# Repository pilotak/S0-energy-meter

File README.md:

# S0 energy meter
ESP8266 based pulse counter for home utility meter compatible with ESPHome, Tasmota, etc.

## Basic model

**Features**:
- 230V direct power supply
- 5x S0 pulse meter input
- [ESPHome config](./config/S0-energy-meter.yaml)

## Enhanced model

**Features**:
- 230V direct power supply
- 1x S0 pulse meter input
- 2x input ie. for button or door sensor
- 1x SSR relay for light
- doorbell detection
- [ESPHome config](./config/S0-energy-meter-switch.yaml)

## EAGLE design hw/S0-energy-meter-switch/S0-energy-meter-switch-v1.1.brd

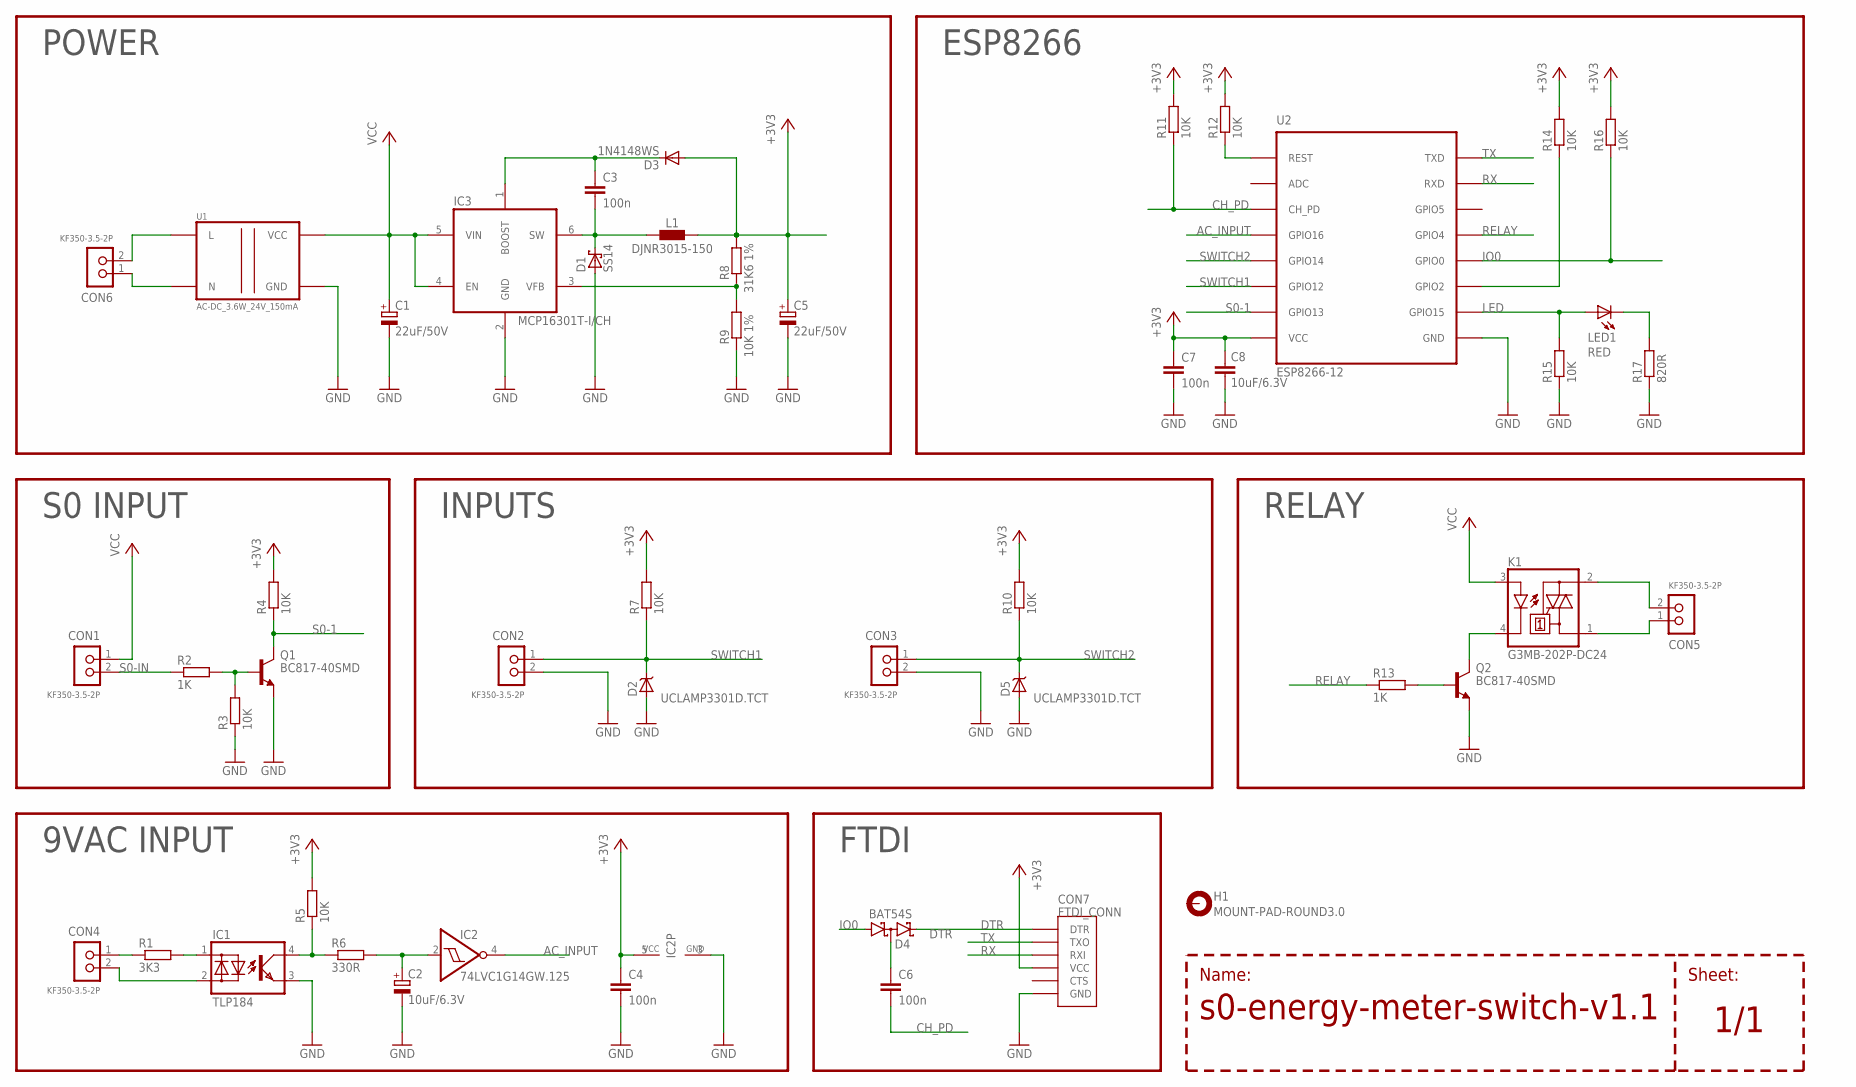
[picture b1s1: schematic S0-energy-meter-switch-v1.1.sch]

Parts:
C1, C5: 22uF/50V; PANASONIC_C
C2: 10uF/6.3V; CT3528
C3, C4, C6, C7: 100n; C0805
C8: 10uF/6.3V; C0805
CON1, CON2, CON3, CON4, CON5, CON6: KF350-3.5-2P; KF350-3.50-2P
CON7: FTDI_CONN; FTDI
D1: SS14; DO214AC
D2, D5: UCLAMP3301D.TCT; SOD323
D3: 1N4148WS; SOD323
D4: BAT54S; SOT23
H1: MOUNT-PAD-ROUND3.0; 3,0-PAD
IC1: TLP184; SOP04
IC2: 74LVC1G14GW.125; SC70-5
IC3: MCP16301T-I/CH; SOT23-6
K1: G3MB-202P-DC24; G3MB
L1: DJNR3015-150; L3015
LED1: RED; LED0805
Q1, Q2: BC817-40SMD; SOT23-BEC
R1: 3K3; R1206
R2, R13: 1K; R0805
R3, R4, R5, R7, R10, R11, R12, R14, R15, R16: 10K; R0805
R6: 330R; R0805
R8: 31K6 1%; R0805
R9: 10K 1%; R0805
R17: 820R; R0805
U1: AC-DC_3.6W_24V_150mA; AC_DC_24V_150MA
U2: ESP8266-12; ESP-12

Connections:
4: IC1.1 (A), R1.2
+3V3: C4.1, C5.+, C7.1, C8.1, CON7.P$4 (VCC), D3.A, IC2.5 (VCC), L1.1, R4.2, R5.2, R7.2, R8.2, R10.2, R11.2, R12.2, R14.2, R16.2, U2.VCC
AC_INPUT: IC2.4 (O), U2.GPIO16
CH: C6.1, D4.3 (C1A2)
CH_PD: C6.2, R11.1, U2.CH_PD
DTR: CON7.P$1 (DTR), D4.2 (C2)
GND: C1.-, C2.-, C4.2, C5.-, C7.2, C8.2, CON2.2, CON3.2, CON7.P$6 (GND), D1.A, D2.A, D5.A, IC1.3 (EMIT), IC2.3 (GND), IC3.2 (GND), Q1.E, Q2.E, R3.1, R9.1, R15.1, R17.1, U1.GND, U2.GND
IO0: D4.1 (A1), R16.1, U2.GPIO0
L: CON6.2, U1.L
LED: LED1.A, R15.2, U2.GPIO15
N: CON6.1, U1.N
unnamed: LED1.C, R17.2
unnamed: CON5.1, K1.1 (A1)
unnamed: Q1.B, R2.2, R3.2
unnamed: C2.+, IC2.2 (I), R6.2
unnamed: CON5.2, K1.2 (A2)
unnamed: CON4.2, IC1.2 (C)
unnamed: IC1.4 (COL), R5.1, R6.1
unnamed: K1.4 (C), Q2.C
unnamed: Q2.B, R13.2
unnamed: R12.1, U2.REST
unnamed: CON4.1, R1.1
unnamed: R14.1, U2.GPIO2
unnamed: C3.2, D1.C, IC3.6 (SW), L1.2
unnamed: C3.1, D3.C, IC3.1 (BOOST)
unnamed: IC3.3 (VFB), R8.1, R9.2
RELAY: R13.1, U2.GPIO4
RX: CON7.P$3 (RXI), U2.RXD
S0-1: Q1.C, R4.1, U2.GPIO13
S0-IN: CON1.2, R2.1
SWITCH1: CON2.1, D2.C, R7.1, U2.GPIO12
SWITCH2: CON3.1, D5.C, R10.1, U2.GPIO14
TX: CON7.P$2 (TXO), U2.TXD
VCC: C1.+, CON1.1, IC3.4 (EN), IC3.5 (VIN), K1.3 (A), U1.VCC

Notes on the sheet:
POWER
ESP8266
S0 INPUT
RELAY
9VAC INPUT
INPUTS
FTDI
Sheet:
Name:

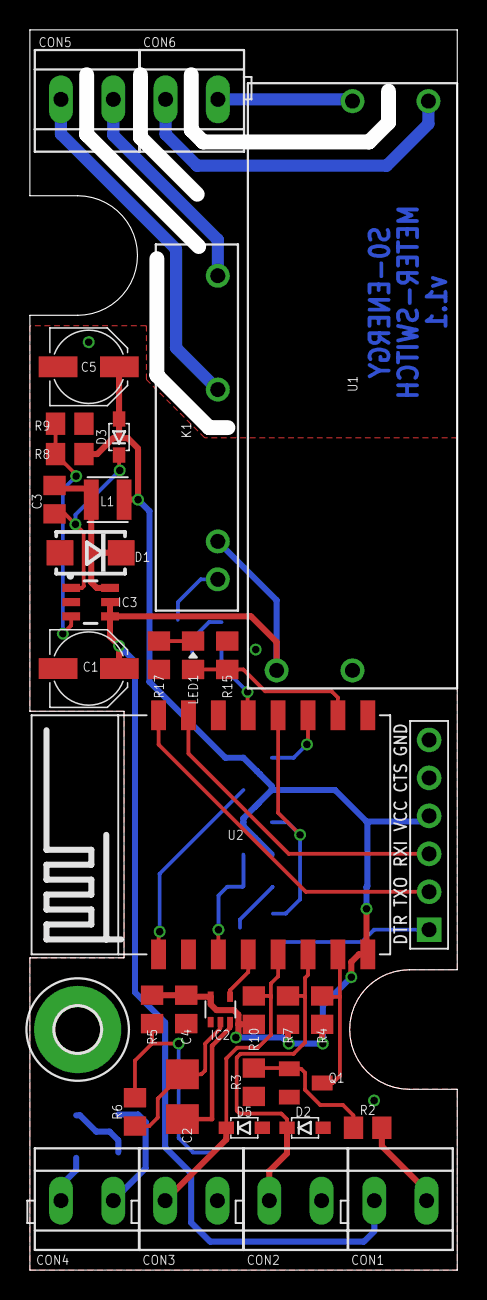
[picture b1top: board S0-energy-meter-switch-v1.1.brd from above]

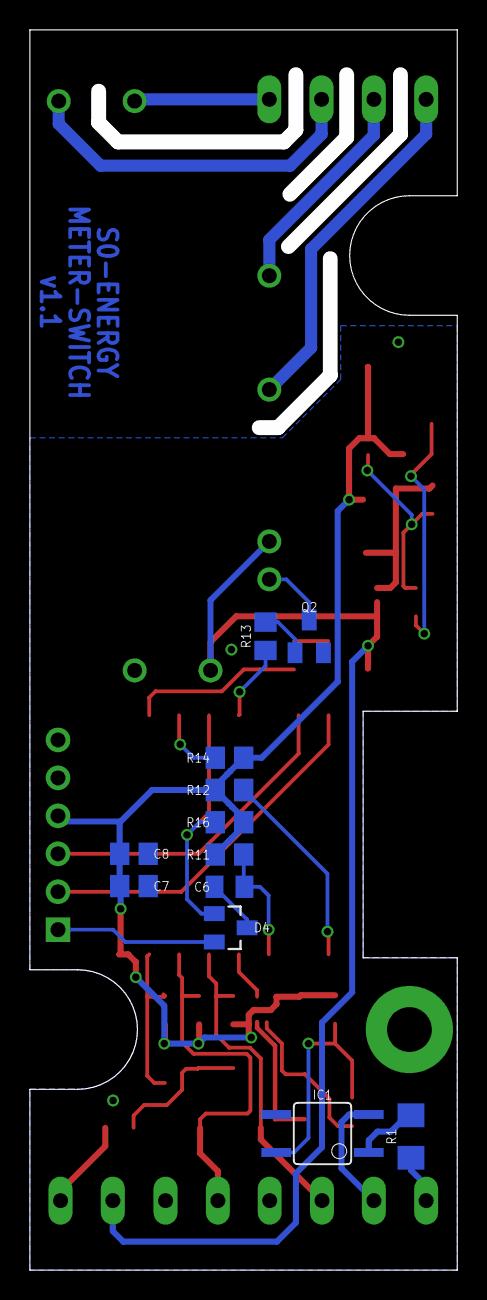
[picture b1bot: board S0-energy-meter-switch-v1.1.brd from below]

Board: 2 copper layers, 27.6 x 82.0 mm, 48 parts (12 on the bottom side), 34 nets.

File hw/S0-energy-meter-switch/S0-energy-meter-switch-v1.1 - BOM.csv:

Qty,Value,Package,Description,Part
2,22uF/50V,PANASONIC_C,Aluminium Capacitor,"C1, C5"
1,10uF/6.3V,CT3528,Tantalum Capacitor,C2
3,100n,C0805,Ceramic Capacitor,"C3, C4, C7"
1,100n,C0805,Ceramic Capacitor,C6
1,10uF/6.3V,C0805,Ceramic Capacitor,C8
6,KF350-3.5-2P,KF350-3.50-2P,Screw terminal 3.5mm pitch,"CON1, CON2, CON3, CON4, CON5, CON6"
1,SS14,DO214AC,Schottky Barrier Rectifier,D1
2,UCLAMP3301D.TCT,SOD323,Low Voltage μClamp TVS diode,"D2, D5"
1,1N4148WS,SOD323,Fast Switching Diode,D3
1,BAT54S,SOT23,Schottky Diodes,D4
1,TLP184,SOP04,AC Photocoupler,IC1
1,74LVC1G14GW.125,SC70-5,Single Schmitt-Trigger Inverter Gate,IC2
1,MCP16301T-I/CH,SOT23-6,High-Voltage Step-Down Regulator,IC3
1,G3MB-202P-DC24,G3MB,"SSR Relay Zero Cross 2A, 100-240 VAC",K1
1,DJNR3015-150,L3015,SMD Power Coil,L1
1,RED,LED0805,SMD LED Diode,LED1
2,BC817-40SMD,SOT23-BEC,NPN Transistor,"Q1, Q2"
1,3K3,R1206,Resistor,R1
2,1K,R0805,Resistor,"R2, R13"
10,10K,R0805,Resistor,"R3, R4, R5, R7, R10, R11, R12, R14, R15, R16"
1,330R,R0805,Resistor,R6
1,31K6 1%,R0805,Resistor,R8
1,10K 1%,R0805,Resistor,R9
1,820R,R0805,Resistor,R17
1,AC-DC_3.6W_24V_150mA,Module,AC-DC regulator,U1
1,ESP8266-12,ESP-12,WIFI Module,U2

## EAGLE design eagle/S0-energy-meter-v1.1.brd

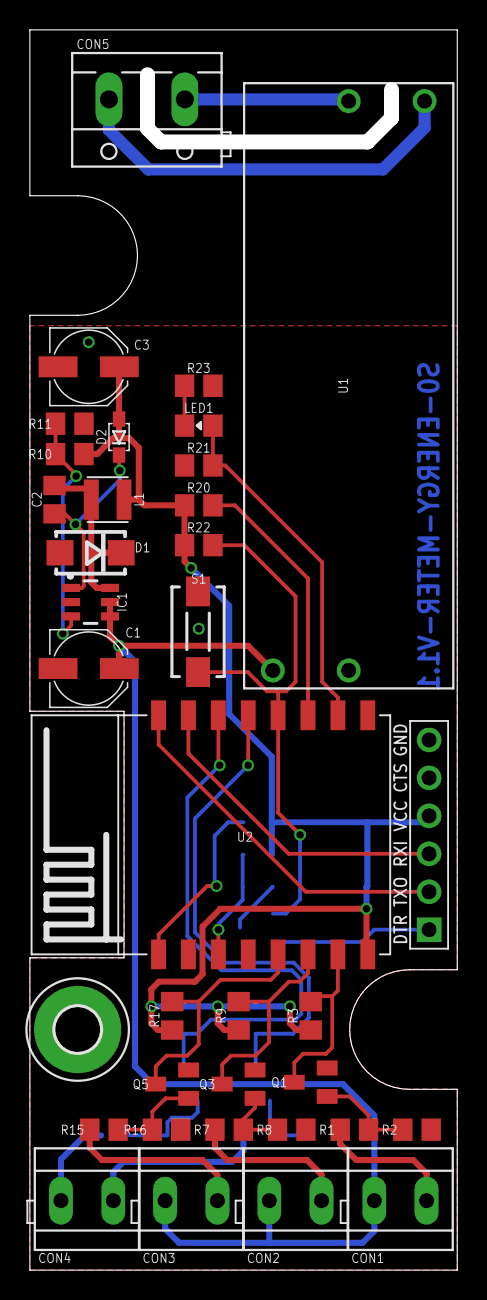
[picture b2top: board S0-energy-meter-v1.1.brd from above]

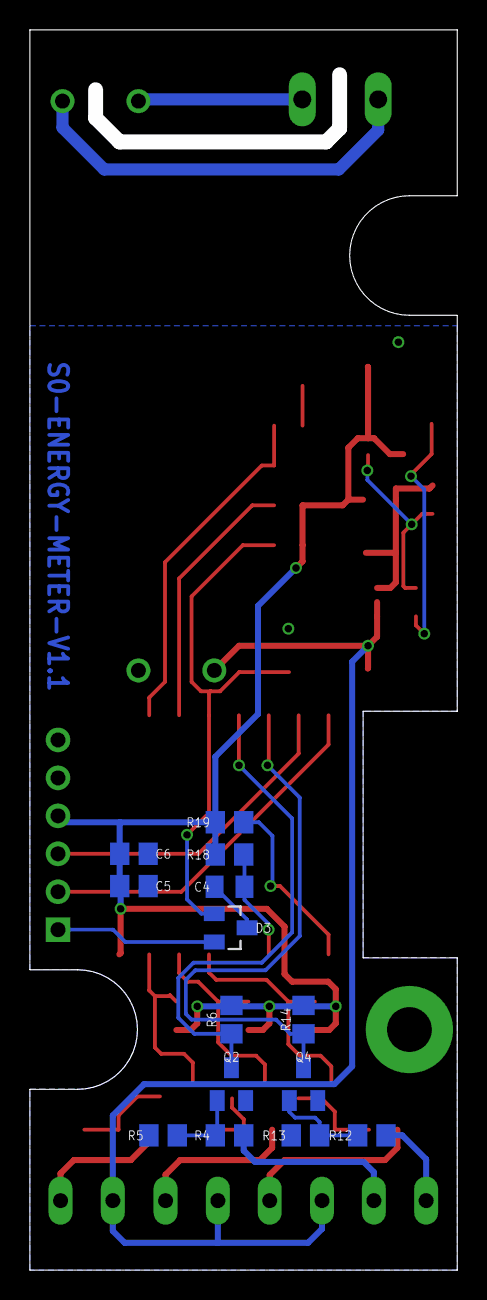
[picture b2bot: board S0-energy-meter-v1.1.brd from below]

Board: 2 copper layers, 27.6 x 82.0 mm, 50 parts (14 on the bottom side), 33 nets.

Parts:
C1, C3: 22uF/50V; PANASONIC_C
C2, C4, C5: 100n; C0805
C6: 10uF/6.3V; C0805
CON1, CON2, CON3, CON4: KF350-3.5-2P; KF350-3.50-2P
CON5: KF301-5.08-2P
CON6: FTDI_CONN; FTDI
D1: SS14; DO214AC
D2: 1N4148WS; SOD323
D3: BAT54S; SOT23
H1: MOUNT-PAD-ROUND3.0; 3,0-PAD
IC1: MCP16301T-I/CH; SOT23-6
L1: DJNR3015-150; L3015
LED1: RED; LED0805
Q1, Q2, Q3, Q4, Q5: BC817-40SMD; SOT23-BEC
R1, R4, R7, R12, R15: 1K; R0805
R2, R3, R5, R6, R8, R9, R13, R14, R16, R17, R18, R19, R20, R21, R22: 10K; R0805
R10: 31K6 1%; R0805
R11: 10K 1%; R0805
R23: 820R; R0805
S1: DTSM-3
U1: AC-DC_3.6W_24V_150mA; AC_DC_24V_150MA
U2: ESP8266-12; ESP-12

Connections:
+3V3: C3.+, C5.1, C6.1, CON6.P$4, D2.A, L1.1, R3.2, R6.2, R9.2, R10.2, R14.2, R17.2, R18.2, R19.2, R20.2, R22.2, U2.VCC
BUTTON: D3.1, R22.1, S1.2, U2.GPIO0
CH: C4.1, D3.3
CH_PD: C4.2, R18.1, U2.CH_PD
DTR: CON6.P$1, D3.2
GND: C1.-, C3.-, C5.2, C6.2, CON6.P$6, D1.A, IC1.2, Q1.E, Q2.E, Q3.E, Q4.E, Q5.E, R2.1, R5.1, R8.1, R11.1, R13.1, R16.1, R21.1, R23.1, S1.1, U1.GND, U2.GND
IN1: CON1.2, R1.1
IN2: CON2.2, R7.1
IN3: CON3.2, R15.1
IN4: CON4.2, R4.1
IN5: CON4.1, R12.1
LED: LED1.A, R21.2, U2.GPIO15
unnamed: LED1.C, R23.2
unnamed: Q1.B, R1.2, R2.2
unnamed: Q3.B, R7.2, R8.2
unnamed: Q5.B, R15.2, R16.2
unnamed: Q2.B, R4.2, R5.2
unnamed: R19.1, U2.REST
unnamed: CON5.2, U1.L
unnamed: CON5.1, U1.N
unnamed: Q4.B, R12.2, R13.2
unnamed: C2.2, D1.C, IC1.6, L1.2
unnamed: C2.1, D2.C, IC1.1
unnamed: IC1.3, R10.1, R11.2
unnamed: R20.1, U2.GPIO2
RX: CON6.P$3, U2.RXD
S0-1: Q1.C, R3.1, U2.GPIO13
S0-2: Q3.C, R9.1, U2.GPIO12
S0-3: Q5.C, R17.1, U2.GPIO14
S0-4: Q2.C, R6.1, U2.GPIO4
S0-5: Q4.C, R14.1, U2.GPIO5
TX: CON6.P$2, U2.TXD
VCC: C1.+, CON1.1, CON2.1, CON3.1, IC1.4, IC1.5, U1.VCC

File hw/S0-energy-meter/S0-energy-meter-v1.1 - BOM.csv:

Qty,Value,Package,Description,Part
2,22uF/50V,PANASONIC_C,Aluminium Capacitor,"C1, C3"
2,100n,C0805,Ceramic Capacitor,"C2, C5"
1,100n,C0805,Ceramic Capacitor,C4
1,10uF/6.3V,C0805,Ceramic Capacitor,C6
4,KF350-3.5-2P,KF350-3.50-2P,2P Screw terminal 3.5mm pitch,"CON1, CON2, CON3, CON4"
1,KF301-5.08-2P,KF301-5.08-2P,2P Screw terminal 5.08mm pitch,CON5
1,SS14,DO214AC,Schottky Barrier Rectifier,D1
1,1N4148WS,SOD323,Fast Switching Diode,D2
1,BAT54S,SOT23,Schottky Diodes,D3
1,MCP16301T-I/CH,SOT23-6,High-Voltage Step-Down Regulator,IC1
1,DJNR3015-150,L3015,SMD Power Coil,L1
1,RED,LED0805,SMD LED Diode,LED1
5,BC817-40SMD,SOT23-BEC,NPN Transistor,"Q1, Q2, Q3, Q4, Q5"
5,1K,R0805,Resistor,"R1, R4, R7, R12, R15"
15,10K,R0805,Resistor,"R2, R3, R5, R6, R8, R9, R13, R14, R16, R17, R18, R19, R20, R21, R22"
1,31K6 1%,R0805,Resistor,R10
1,10K 1%,R0805,Resistor,R11
1,820R,R0805,Resistor,R23
1,DTSM-3,DTSM-3,Push Button,S1
1,AC-DC_3.6W_24V_150mA,Module,AC-DC regulator,U1
1,ESP8266-12,ESP-12,WIFI Module,U2

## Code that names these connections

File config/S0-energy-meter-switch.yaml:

esphome:
  name: "Energy meter swtich"
  platform: ESP8266
  board: esp01_1m
  esp8266_restore_from_flash: True

wifi:
  fast_connect: true
  networks:
  - ssid: !secret ssid
    password: !secret password

logger:

# Enable Home Assistant API
api:

ota:

sensor:
  - platform: pulse_counter
    pin: GPIO13
    name: "Power consumption 1"
    id: power1
    unit_of_measurement: 'Wh'
    internal_filter: 10ms
    filters:
      - multiply: 16.66666666666
    count_mode:
      rising_edge: DISABLE
      falling_edge: INCREMENT

  - platform: total_daily_energy
    name: "Daily power consumption 1"
    icon: "mdi:current-ac"
    power_id: power1
    unit_of_measurement: 'kWh'
    filters:
      - multiply: 0.001

output:
  - platform: gpio
    pin: GPIO4
    id: relay

light:
  - platform: binary
    name: "Light 1"
    id: light1
    output: relay

binary_sensor:
  - platform: status
    name: "Energy meter switch: status"

  - platform: gpio
    name: "Doorbell"
    pin:
      number: GPIO16
      inverted: False

  - platform: gpio
    name: "Door sensor"
    device_class: door
    pin:
      number: GPIO14
      inverted: True

  - platform: gpio
    name: "Switch 1"
    on_press:
      then:
        - light.turn_on: light1
    on_release:
      then:
        - light.turn_off: light1
    pin:
      number: GPIO12
      inverted: True

time:
  - platform: homeassistant
    id: homeassistant_time
    timezone: "Europe/Prague"
    
status_led:
  pin:
    number: GPIO15

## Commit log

2020-11-10 init
2020-11-10 folder restructure
2020-11-10 add meter with switch
2021-05-27 readme
2021-05-27 images update
